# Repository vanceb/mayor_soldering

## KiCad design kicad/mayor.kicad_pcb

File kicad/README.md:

## ATTiny85 driven Neopixels

* [Good Background](https://www.instructables.com/Use-a-1-ATTiny-to-drive-addressable-RGB-LEDs/)

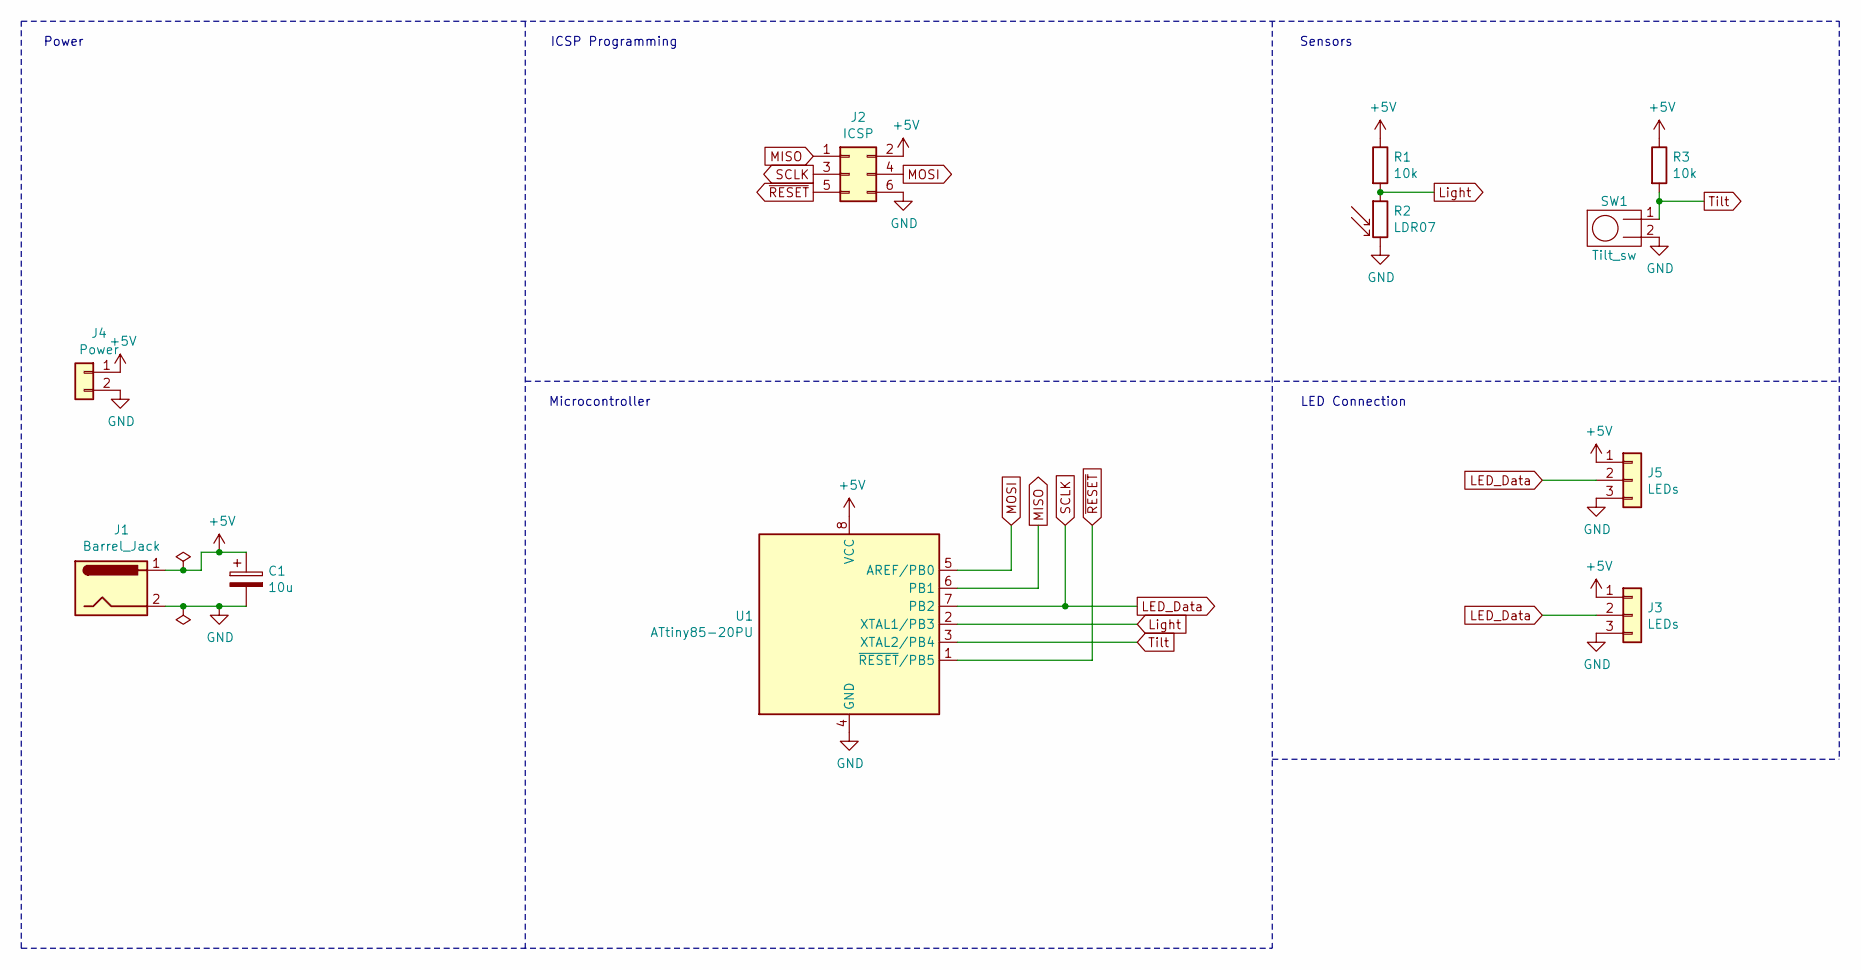
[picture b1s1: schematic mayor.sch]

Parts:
C1: 10u; CP_Radial_D5.0mm_P2.50mm
J1: Barrel_Jack; BarrelJack_Horizontal
J2: ICSP; PinHeader_2x03_P2.54mm_Vertical
J3: LEDs; JST_PH_S3B-PH-K_1x03_P2.00mm_Horizontal
J4: Power; PinHeader_1x02_P2.54mm_Vertical
J5: LEDs; PinHeader_1x03_P2.54mm_Vertical
R1, R3: 10k; R_Axial_DIN0207_L6.3mm_D2.5mm_P10.16mm_Horizontal
R2: LDR07; R_LDR_5.1x4.3mm_P3.4mm_Vertical
SW1: Tilt_sw; Tilt
U1: ATtiny85-20PU; DIP-8_W7.62mm

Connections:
+5V: C1.1, J1.1, J2.2, J3.1, J4.1, J5.1, R1.1, R3.1, U1.8 (VCC)
GND: C1.2, J1.2, J2.6, J3.3, J4.2, J5.3, R2.2, SW1.2, U1.4 (GND)
LED_Data: J2.3, J3.2, J5.2, U1.7 (PB2)
Light: R1.2, R2.1, U1.2 (XTAL1/PB3)
MISO: J2.1, U1.6 (PB1)
MOSI: J2.4, U1.5 (AREF/PB0)
Tilt: R3.2, SW1.1, U1.3 (XTAL2/PB4)
~RESET: J2.5, U1.1 (~RESET~/PB5)

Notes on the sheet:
Power
ICSP Programming
Sensors
LED Connection
Microcontroller

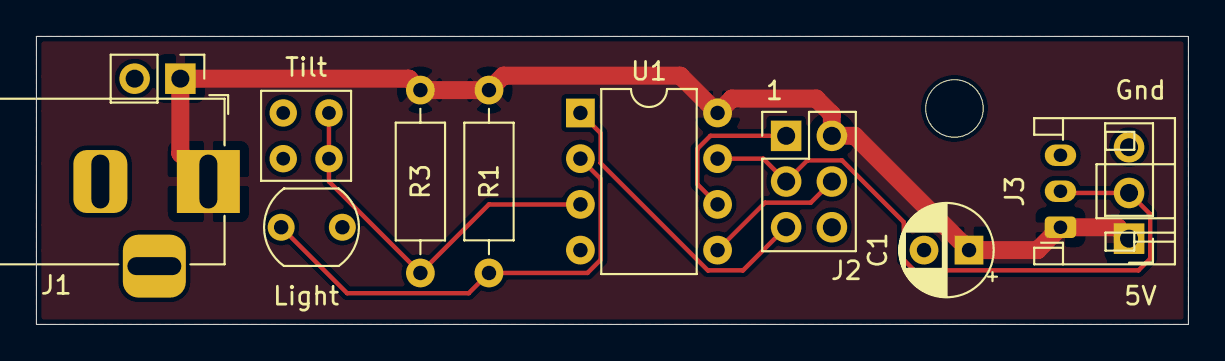
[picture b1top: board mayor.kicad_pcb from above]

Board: 2 copper layers, 64.0 x 16.0 mm, 11 parts (0 on the bottom side), 8 nets.
